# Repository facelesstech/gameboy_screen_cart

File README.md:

# gameboy_screen_cart
gameboy_screen_cart

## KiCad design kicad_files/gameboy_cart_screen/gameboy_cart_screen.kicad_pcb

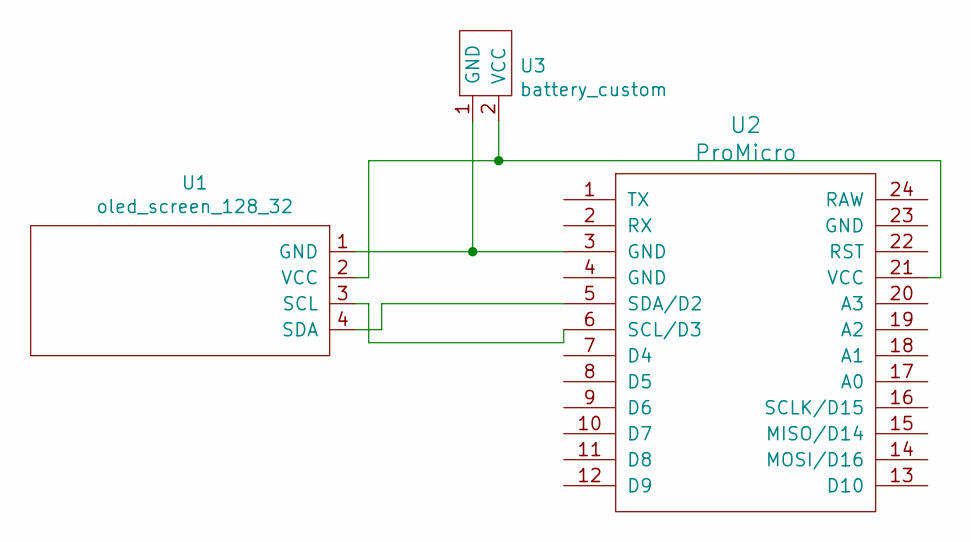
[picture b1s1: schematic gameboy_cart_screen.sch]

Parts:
U1: oled_screen_128_32; oled_128_32
U2: ProMicro; ProMicro_smd_pads
U3: battery_custom; vcc_gnd_2pin_custom

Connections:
unnamed: U1.1 (GND), U2.3 (GND), U3.1 (GND)
unnamed: U1.2 (VCC), U2.21 (VCC), U3.2 (VCC)
unnamed: U1.3 (SCL), U2.6 (SCL/D3)
unnamed: U1.4 (SDA), U2.5 (SDA/D2)

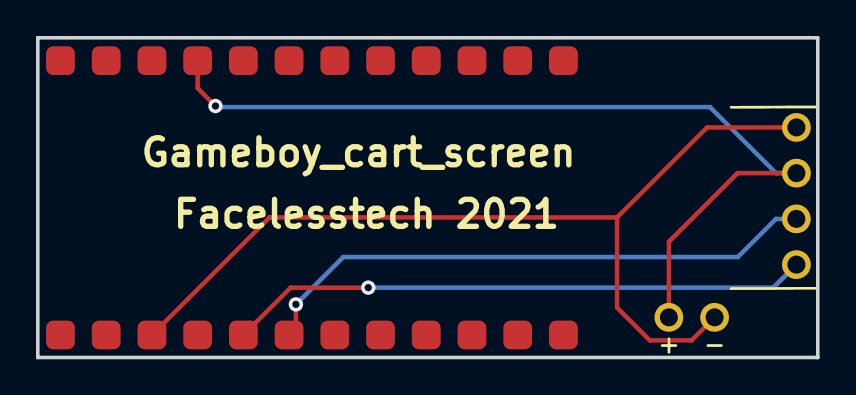
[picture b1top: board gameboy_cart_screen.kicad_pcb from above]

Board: 2 copper layers, 43.3 x 17.8 mm, 3 parts (0 on the bottom side), 4 nets.

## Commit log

2021-05-31 3d print files
2021-05-31 arduino files
2021-05-31 kicad board files
